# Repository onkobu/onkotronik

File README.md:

# onkotronik
Onkobu Tanaake's Electronic Projects

The repository splits into two major parts. One contains the libraries used
to create the artifacts. Second the projects themself are stored next to the
libs.

## Nippelbrett

## Spielzeugherd

## Sidelight (WS2812)
5 WS2812-breakout boards make up a cube with 4 sides and a lid. Underneath
fits a ATTiny microcontroller with a tiny little program inside. Its main
purpose is to replace the flimsy electronic candle lights with a single
LED and a coin cell battery with more power. In addition it brings also
more color. [More…](sidelight/README.md)

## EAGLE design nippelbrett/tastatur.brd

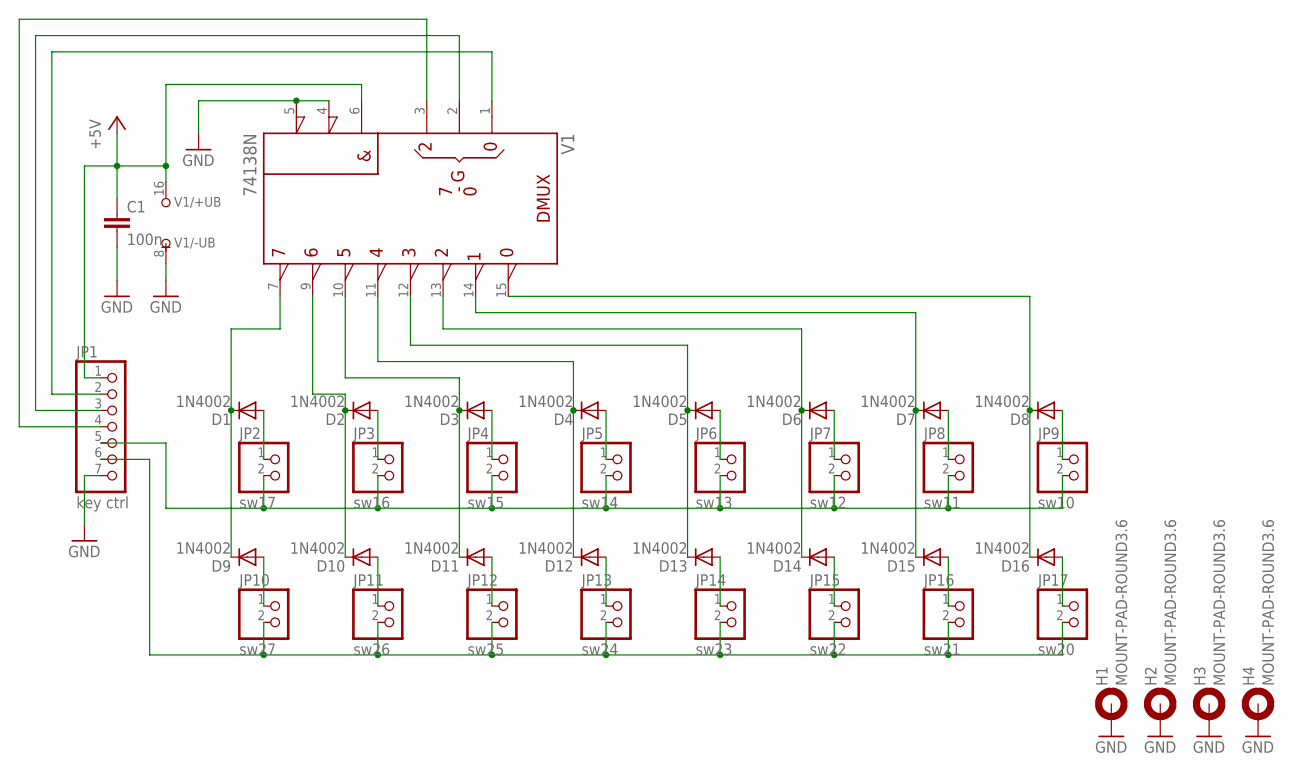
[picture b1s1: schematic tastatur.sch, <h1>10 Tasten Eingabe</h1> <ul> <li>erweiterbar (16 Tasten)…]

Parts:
C1: 100n; C050-024X044
D1, D2, D3, D4, D5, D6, D7, D8, D9, D10, D11, D12, D13, D14, D15, D16: 1N4002; DO41-7.6
H1, H2, H3, H4: MOUNT-PAD-ROUND3.6; 3,6-PAD
JP1: key ctrl; 1X07
JP2: sw17; 1X02
JP3: sw16; 1X02
JP4: sw15; 1X02
JP5: sw14; 1X02
JP6: sw13; 1X02
JP7: sw12; 1X02
JP8: sw11; 1X02
JP9: sw10; 1X02
JP10: sw27; 1X02
JP11: sw26; 1X02
JP12: sw25; 1X02
JP13: sw24; 1X02
JP14: sw23; 1X02
JP15: sw22; 1X02
JP16: sw21; 1X02
JP17: sw20; 1X02
V1: 74138N; DIL16

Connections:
+5V: C1.1, JP1.1, V1.6 (G1), V1.16 (+UB)
ADDR0: JP1.2, V1.1 (A)
ADDR1: JP1.3, V1.2 (B)
ADDR2: JP1.4, V1.3 (C)
COL3: D5.C, D13.C, V1.12 (Y3)
COL4: D4.C, D12.C, V1.11 (Y4)
COL5: D3.C, D11.C, V1.10 (Y5)
COL6: D2.C, D10.C, V1.9 (Y6)
COL7: D1.C, D9.C, V1.7 (Y7)
GND: C1.2, H1.B3,6, H2.B3,6, H3.B3,6, H4.B3,6, JP1.7, V1.4 (!G2A), V1.5 (!G2B), V1.8 (-UB)
IN0: JP1.5, JP2.2, JP3.2, JP4.2, JP5.2, JP6.2, JP7.2, JP8.2, JP9.2
IN1: JP1.6, JP10.2, JP11.2, JP12.2, JP13.2, JP14.2, JP15.2, JP16.2, JP17.2
unnamed: D6.C, D14.C, V1.13 (Y2)
unnamed: D7.C, D15.C, V1.14 (Y1)
unnamed: D8.C, D16.C, V1.15 (Y0)
unnamed: D6.A, JP7.1
unnamed: D7.A, JP8.1
unnamed: D8.A, JP9.1
unnamed: D14.A, JP15.1
unnamed: D5.A, JP6.1
unnamed: D13.A, JP14.1
unnamed: D4.A, JP5.1
unnamed: D12.A, JP13.1
unnamed: D11.A, JP12.1
unnamed: D3.A, JP4.1
unnamed: D2.A, JP3.1
unnamed: D10.A, JP11.1
unnamed: D9.A, JP10.1
unnamed: D1.A, JP2.1
unnamed: D15.A, JP16.1
unnamed: D16.A, JP17.1

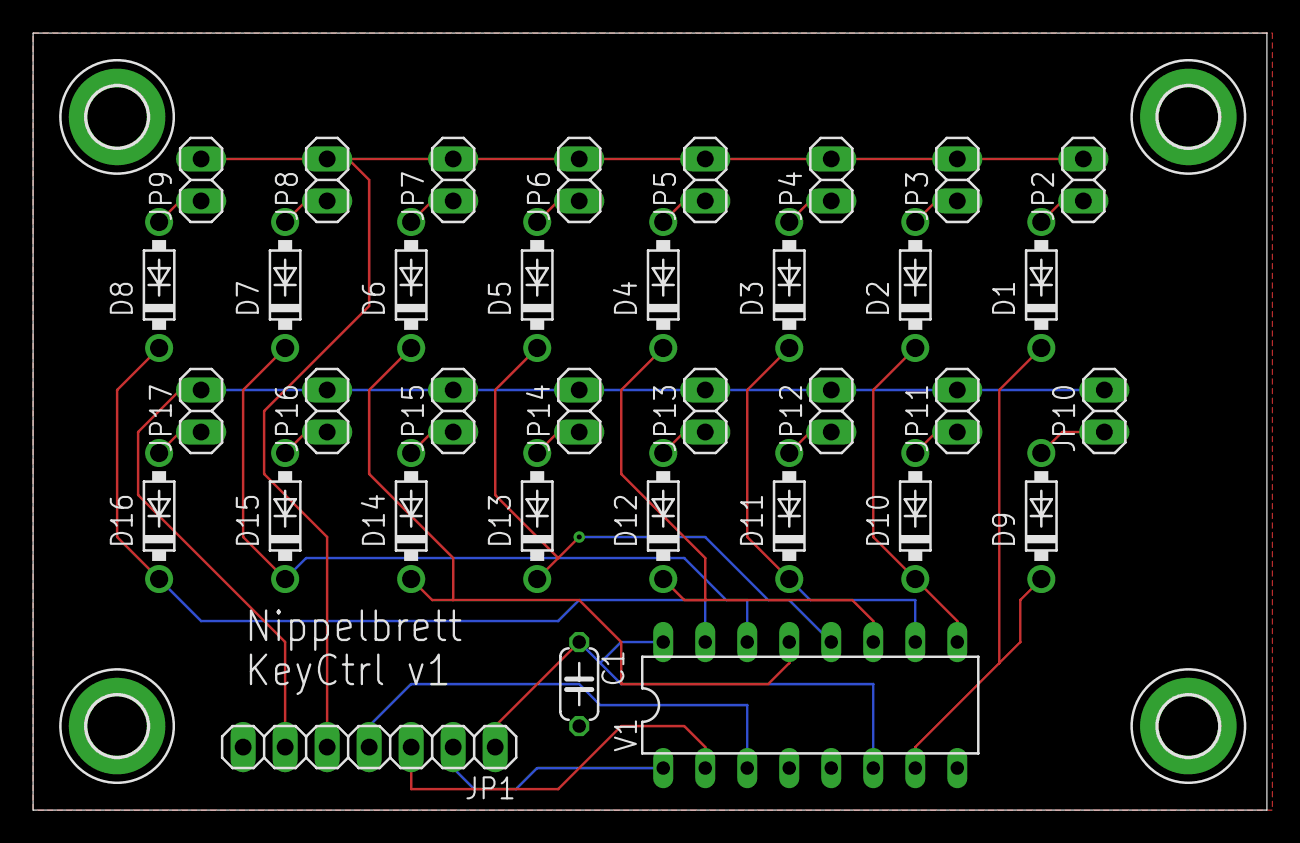
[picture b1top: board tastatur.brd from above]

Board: 2 copper layers, 74.6 x 47.0 mm, 39 parts (0 on the bottom side), 31 nets.

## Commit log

2015-03-07 Nippelbrett initial
2015-07-13 Spielzeugherd initialisierenwq
2015-11-21 README erweitern
2015-11-21 Sidelight and README
2015-11-21 Main README with relative link
2016-05-16 Extended behavior to have Categories
    Extended file naming and selection by category and Number.
    Now there are nine of the ten keys for sounds and one key for switching
    through the categories.
